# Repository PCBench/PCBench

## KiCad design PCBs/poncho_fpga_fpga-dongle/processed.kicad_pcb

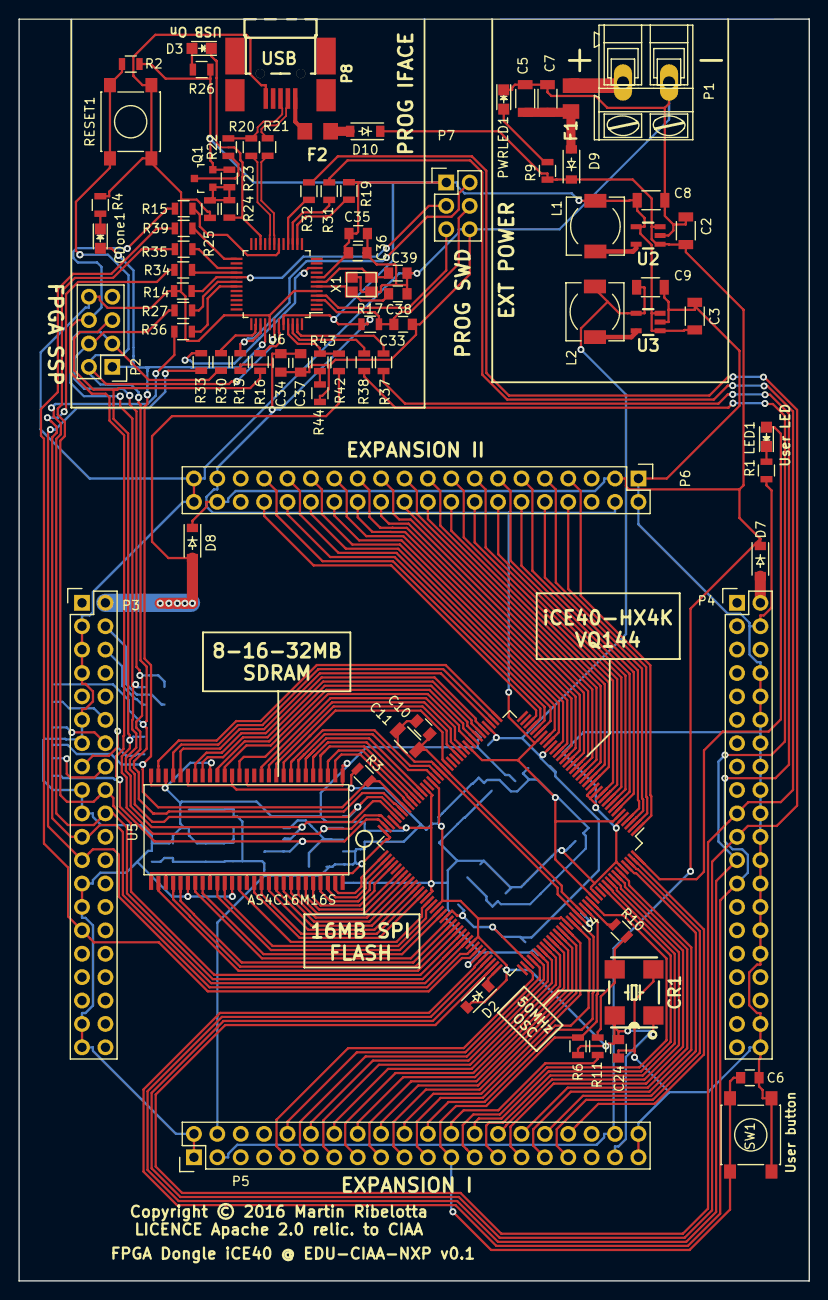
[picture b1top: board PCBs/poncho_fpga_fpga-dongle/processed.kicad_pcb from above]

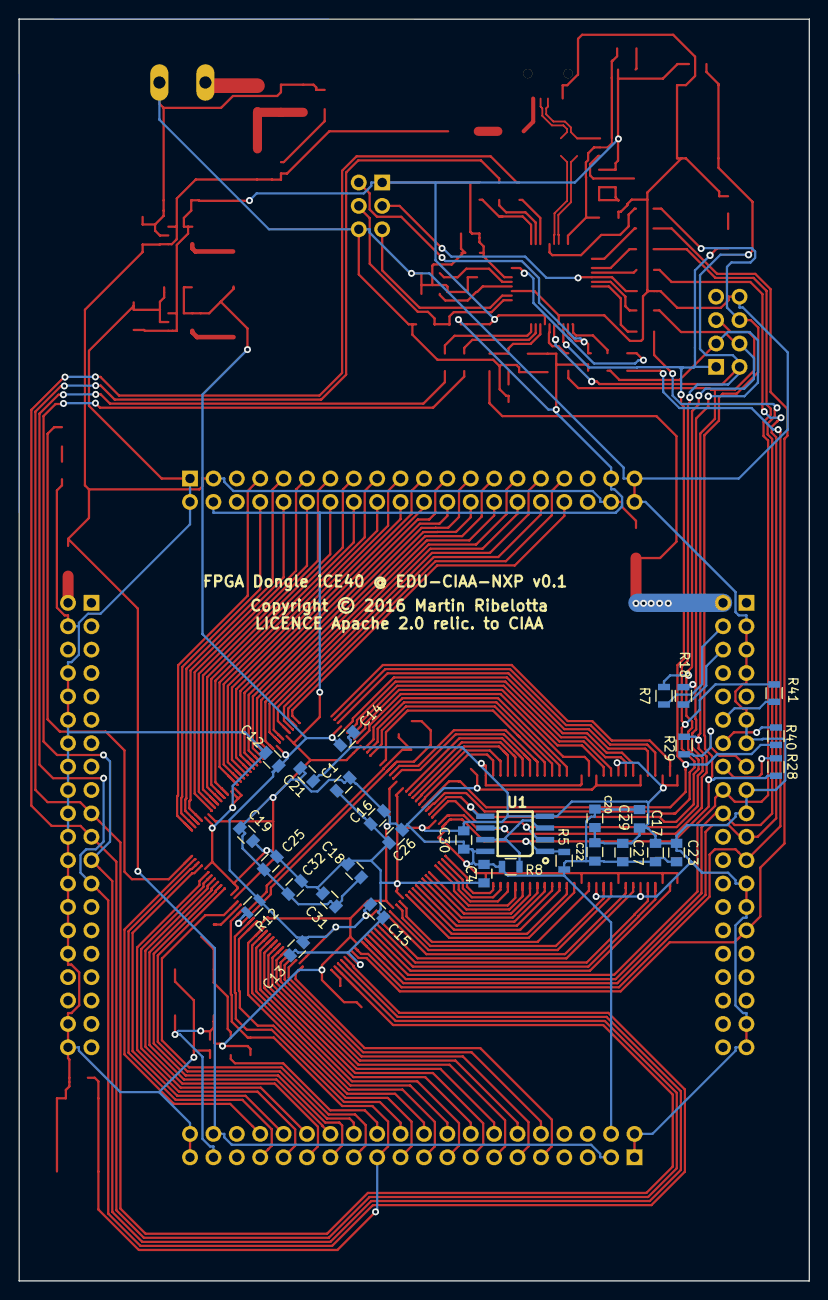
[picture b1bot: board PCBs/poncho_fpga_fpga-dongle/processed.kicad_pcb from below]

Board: 2 copper layers, 85.8 x 137.0 mm, 114 parts (31 on the bottom side), 166 nets.

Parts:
C1, C4, C6, C10, C12, C13, C14, C15, C16, C17, C18, C19, C20, C21, C22, C23, C24, C25, C26, C27, C29, C30, C31, C32, C33, C34, C36: 100nF; C_0805
C2, C3: 22uF; C_1206
C5, C7: 47uF; C_1206
C8, C9, C11: 10uF; C_1206
C35, C37: 10nF; C_0805
C38, C39: 18pF; C_0805
CDone1: LED/Green/0805; LED-0805
CR1: Oscillator-50MHZ_TXC-7W; Oscillator_7.0x5.0mm
D2, D7, D8, D9, D10: 1N5819(S4SOD-123); SOD-123
D3: LED/Red/0805; LED-0805
F1, F2: 1A; FUSE-1206
L1, L2: 2.2uH; Choke_SMD_6.3x6.3_H3
LED1: LED/Red/0805; LED-0805
P1: CONN_01X02; AK300-2
P2: PGM; Pin_Header_Straight_2x04
P3: right; Pin_Header_Straight_2x20
P4: left; Pin_Header_Straight_2x20
P5, P6: CONN_01X40; Pin_Header_Straight_2x20
P7: DBG_SWD; Pin_Header_Straight_2x03
P8: USB_PWR; USB_Mini-B-NOSILK
PWRLED1: LED/Red/0805; LED-0805
Q1: BC857; SOT-23
R1, R3, R9, R19, R24, R26: 2.2k; R_0805
R2, R5, R6, R8, R13, R14, R17, R23, R42, R43, R44: 10k; R_0805
R4, R10, R11, R15, R16, R27, R30: 22R; R_0805
R7, R12, R18, R28, R29, R31, R32, R33, R34, R35, R36, R37, R38, R39, R40, R41: 100R; R_0805
R20, R21: 33R; R_0805
R22: 1.5k; R_0805
R25: UL; R_0805
RESET1: T1107A(6x3,8x2,5MM); SW_SPST_PTS645
SW1: T1107A(6x3,8x2,5MM); SW_SPST_PTS645
U1: W25Q128FVSIG(SOIC-8_208mil); SOIC-8_208mil
U2: sc189(Z) 3.3v; SOT-23-5
U3: sc189(C) 1.2v; SOT-23-5
U4: iCE40-HX4K-TQ144; LQFP-144_20x20mm_Pitch0.5mm
U5: AS4C16M16S; TSOP_II_54
U6: LPC11U35FBD48; LQFP-48_7x7mm_Pitch0.5mm
X1: 12MHz; crystal_FA238-TSX3225

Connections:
+1V2: C9.2, C12.1, C13.1, C14.1, C15.1, L2.2, R12.1, U3.4, U4.27, U4.40, U4.92, U4.111
+3V3: C1.2, C3.2, C4.2, C8.2, C16.1, C17.1, C18.1, C19.1, C20.1, C21.1, C22.1, C23.1, C24.1, C25.1, C26.1, C27.1, C29.1, C30.1, C31.1, C32.1, C34.1, C35.1, C36.1, C37.1, CR1.1, CR1.4, D2.2, L1.2, P5.4, P5.37, P6.4, P6.37, P7.1, Q1.2, R2.2, R3.2, R5.2, R6.2, R8.1, R13.1, R17.1, R19.2, R23.1, R26.1, U1.8, U2.4, U3.1, U3.3, U4.6, U4.30, U4.46, U4.57, U4.72, U4.89, U4.100, U4.123, U4.131, U5.1, U5.3, U5.9, U5.14, U5.27, U5.43, U5.49, U6.8, U6.44
+5V: C2.2, D7.1, D8.1, D9.1, D10.1, P5.3, P5.38, P6.3, P6.38, R9.1, U2.1, U2.3
/AUX_CDONE: P3.14, R40.1
/AUX_CRESET: P3.12, R41.1
/AUX_SPI_MISO: P3.4, R7.1
/AUX_SPI_MOSI: P3.6, R18.1
/AUX_SPI_SCK: P3.15, R29.1
/AUX_SPI_SSEL: P3.16, R28.1
/BUT1: C6.2, P5.23, R6.1, SW1.2, U4.128
/CIAA_5V1: D7.2, P4.2
/CIAA_5V2: D8.2, P3.2, R42.2
/DBG_SWCLK: P7.3, R14.1, U6.29
/DBG_SWDIO: P7.2, R13.2, U6.39
/DBG_~ISP~: P7.5, U6.4
/DBG_~RST~: C33.1, P7.4, R17.2, U6.3
/D_USB_N: R21.2, U6.19
/D_USB_P: R20.2, U6.20
/EXTCLK: P5.24, R11.1
/FPGA_IO_BANK1_0: P5.9, U4.110
/FPGA_IO_BANK1_1: P5.10, U4.112
/FPGA_IO_BANK1_2: P5.11, U4.113
/FPGA_IO_BANK1_3: P5.12, U4.114
/FPGA_IO_BANK1_4: P5.13, U4.115
/FPGA_IO_BANK1_5: P5.14, U4.116
/FPGA_IO_BANK1_6: P5.15, U4.117
/FPGA_IO_BANK1_7: P5.16, U4.118
/FPGA_IO_BANK1_8: P5.17, U4.119
/FPGA_IO_BANK1_9: P5.18, U4.120
/FPGA_IO_BANK1_10: P5.19, U4.121
/FPGA_IO_BANK1_11: P5.20, U4.122
/FPGA_IO_BANK1_12: P5.21, U4.124
/FPGA_IO_BANK1_13: P5.22, U4.125
/FPGA_IO_BANK1_14: P5.25, U4.130
/FPGA_IO_BANK1_15: P5.26, U4.134
/FPGA_IO_BANK1_16: P5.27, U4.135
/FPGA_IO_BANK1_17: P5.28, U4.136
/FPGA_IO_BANK1_18: P5.29, U4.137
/FPGA_IO_BANK1_19: P5.30, U4.138
/FPGA_IO_BANK1_20: P5.31, U4.139
/FPGA_IO_BANK1_21: P5.32, U4.141
/FPGA_IO_BANK1_22: P5.33, U4.142
/FPGA_IO_BANK1_23: P5.34, U4.143
/FPGA_IO_BANK2_0: P6.7, U4.1
/FPGA_IO_BANK2_1: P6.8, U4.2
/FPGA_IO_BANK2_2: P6.9, U4.3
/FPGA_IO_BANK2_3: P6.10, U4.4
/FPGA_IO_BANK2_4: P6.11, U4.7
/FPGA_IO_BANK2_5: P6.12, U4.8
/FPGA_IO_BANK2_6: P6.13, U4.9
/FPGA_IO_BANK2_7: P6.14, U4.10
/FPGA_IO_BANK2_8: P6.15, U4.11
/FPGA_IO_BANK2_9: P6.16, U4.12
/FPGA_IO_BANK2_10: P6.17, U4.15
/FPGA_IO_BANK2_11: P6.18, U4.16
/FPGA_IO_BANK2_12: P6.19, U4.17
/FPGA_IO_BANK2_13: P6.20, U4.18
/FPGA_IO_BANK2_14: P6.21, U4.19
/FPGA_IO_BANK2_15: P6.22, U4.20
/FPGA_IO_BANK2_16: P6.23, U4.21
/FPGA_IO_BANK2_17: P6.24, U4.22
/FPGA_IO_BANK2_18: P6.25, U4.23
/FPGA_IO_BANK2_19: P6.26, U4.24
/FPGA_IO_BANK2_20: P6.27, U4.25
/FPGA_IO_BANK2_21: P6.28, U4.26
/FPGA_IO_BANK2_22: P6.29, U4.28
/FPGA_IO_BANK2_23: P6.30, U4.29
/FPGA_IO_BANK2_24: P6.31, U4.31
/FPGA_IO_BANK2_25: P6.32, U4.32
/FPGA_IO_BANK2_26: P6.33, U4.33
/FPGA_IO_BANK2_27: P6.34, U4.34
/FPGM_MISO: R27.1, U6.30
/FPGM_MOSI: R30.1, U6.38
/FPGM_SCK: R16.1, U6.43
/FPGM_SS: R15.1, U6.18
/GNDPLL: C10.1, C11.1, U4.53, U4.127
/GPIO0: P3.29, R39.2, U4.102
/I2C_SCL: P4.21, R32.2, U4.106
/I2C_SDA: P4.19, R31.2, U4.107
/LED1: LED1.2, U4.144
/P_GPIO: R39.1, U6.25
/P_RxD: R38.1, U6.46
/P_SCL: R32.1, U6.16
/P_SDA: R31.1, U6.15
/P_SPI_CLK: R36.1, U6.31
/P_SPI_MISO: R35.1, U6.27
/P_SPI_MOSI: R34.1, U6.28
/P_SPI_SS: R33.1, U6.10
/P_TxD: R37.1, U6.47
/RAM_A1: U4.76, U5.23
/RAM_A2: U4.75, U5.24
/RAM_A3: U4.74, U5.25
/RAM_A4: U4.73, U5.26
/RAM_A5: U4.64, U5.29
/RAM_A6: U4.63, U5.30
/RAM_A7: U4.62, U5.31
/RAM_A8: U4.61, U5.32
/RAM_A9: U4.60, U5.33
/RAM_A10: U4.56, U5.34
/RAM_A11: U4.78, U5.22
/RAM_A12: U4.55, U5.35
/RAM_A13: U4.52, U5.36
/RAM_A14: U4.80, U5.20
/RAM_A15: U4.79, U5.21
/RAM_CAS: U4.83, U5.17
/RAM_CKE: U4.49, U5.37
/RAM_CLK: U4.48, U5.38
/RAM_CS: U4.81, U5.19
/RAM_D0: U4.96, U5.2
/RAM_D1: U4.95, U5.4
/RAM_D2: U4.94, U5.5
/RAM_D3: U4.93, U5.7
/RAM_D4: U4.91, U5.8
/RAM_D5: U4.90, U5.10
/RAM_D6: U4.88, U5.11
/RAM_D7: U4.87, U5.13
/RAM_D8: U4.45, U5.42
/RAM_D9: U4.44, U5.44
/RAM_D10: U4.43, U5.45
/RAM_D11: U4.42, U5.47
/RAM_D12: U4.41, U5.48
/RAM_D13: U4.39, U5.50
/RAM_D14: U4.38, U5.51
/RAM_D15: U4.37, U5.53
/RAM_DQMH: U4.47, U5.39
/RAM_DQML: U4.85, U5.15
/RAM_RAS: U4.82, U5.18
/RAM_RDnWR: U4.84, U5.16
/RxD: P4.23, R38.2, U4.105
/SPI_CLK: P3.20, R36.2, U4.98
/SPI_CS: P3.23, R33.2, U4.101
/SPI_MISO: P3.18, R35.2, U4.97
/SPI_MOSI: P3.21, R34.2, U4.99
/SYSCLK: R10.1, U4.129
/TxD: P4.25, R37.2, U4.104
/USB_N: P8.2, R21.1
/USB_P: P8.3, R20.1, R22.1
/VCCPLL: C10.2, C11.2, R12.2, U4.54, U4.126
/iCE40-CDONE: CDone1.2, P2.1, R3.1, R40.2, U4.65, U6.40
/iCE40-CRESET: P2.2, R2.1, R41.2, RESET1.2, U4.66, U6.42
/iCE40-SCK: P2.5, R16.2, R29.2, U1.6, U4.70
/iCE40-SDI: P2.3, R18.2, R30.2, U1.2, U4.68
/iCE40-SDO: P2.4, R7.2, R27.2, U1.5, U4.67
/iCE40-SS_B: P2.6, R5.1, R15.2, R28.2, U1.1, U4.71
/~USB_CONNECT~: D3.1, R24.2, U6.22
GND: C1.1, C2.1, C3.1, C4.1, C5.1, C6.1, C7.1, C8.1, C9.1, C12.2, C13.2, C14.2, C15.2, C16.2, C17.2, C18.2, C19.2, C20.2, C21.2, C22.2, C23.2, C24.2, C25.2, C26.2, C27.2, C29.2, C30.2, C31.2, C32.2, C33.2, C34.2, C35.2, C36.2, C37.2, C38.2, C39.2, CR1.2, P1.1, P2.8, P3.3, P3.5, P3.7, P3.11, P3.13, P3.17, P3.19, P3.25, P3.27, P3.37, P3.39, P4.4, P4.8, P4.10, P4.12, P4.14, P4.16, P4.18, P4.20, P4.22, P4.24, P4.26, P4.28, P4.30, P4.32, P4.38, P4.40, P5.1, P5.2, P5.39, P5.40, P6.1, P6.2, P6.39, P6.40, P7.6, P8.5, PWRLED1.1, R1.2, R4.2, R14.2, R25.2, R44.1, RESET1.1, SW1.1, U1.4, U2.2, U3.2, U4.5, U4.13, U4.14, U4.59, U4.69, U4.86, U4.103, U4.132, U4.140, U5.6, U5.12, U5.28, U5.41, U5.46, U5.52, U5.54, U6.5, U6.41, X1.3
unnamed: C5.2, C7.2, D9.2, F1.2
unnamed: C38.1, U6.6, X1.2
unnamed: C39.1, U6.7, X1.1
unnamed: CDone1.1, R4.1
unnamed: CR1.3, R10.2, R11.2
unnamed: D2.1, U4.108
unnamed: D3.2, R26.2
unnamed: D10.2, F2.2
unnamed: F1.1, P1.2
unnamed: F2.1, P8.1
unnamed: L1.1, U2.5
unnamed: L2.1, U3.5
unnamed: LED1.1, R1.1
unnamed: PWRLED1.2, R9.2
unnamed: Q1.1, R23.2, R24.1, R25.1
unnamed: Q1.3, R22.2
unnamed: R8.2, U1.3, U1.7
unnamed: R19.1, U6.14
unnamed: R42.1, R43.1, U6.45
unnamed: R43.2, R44.2

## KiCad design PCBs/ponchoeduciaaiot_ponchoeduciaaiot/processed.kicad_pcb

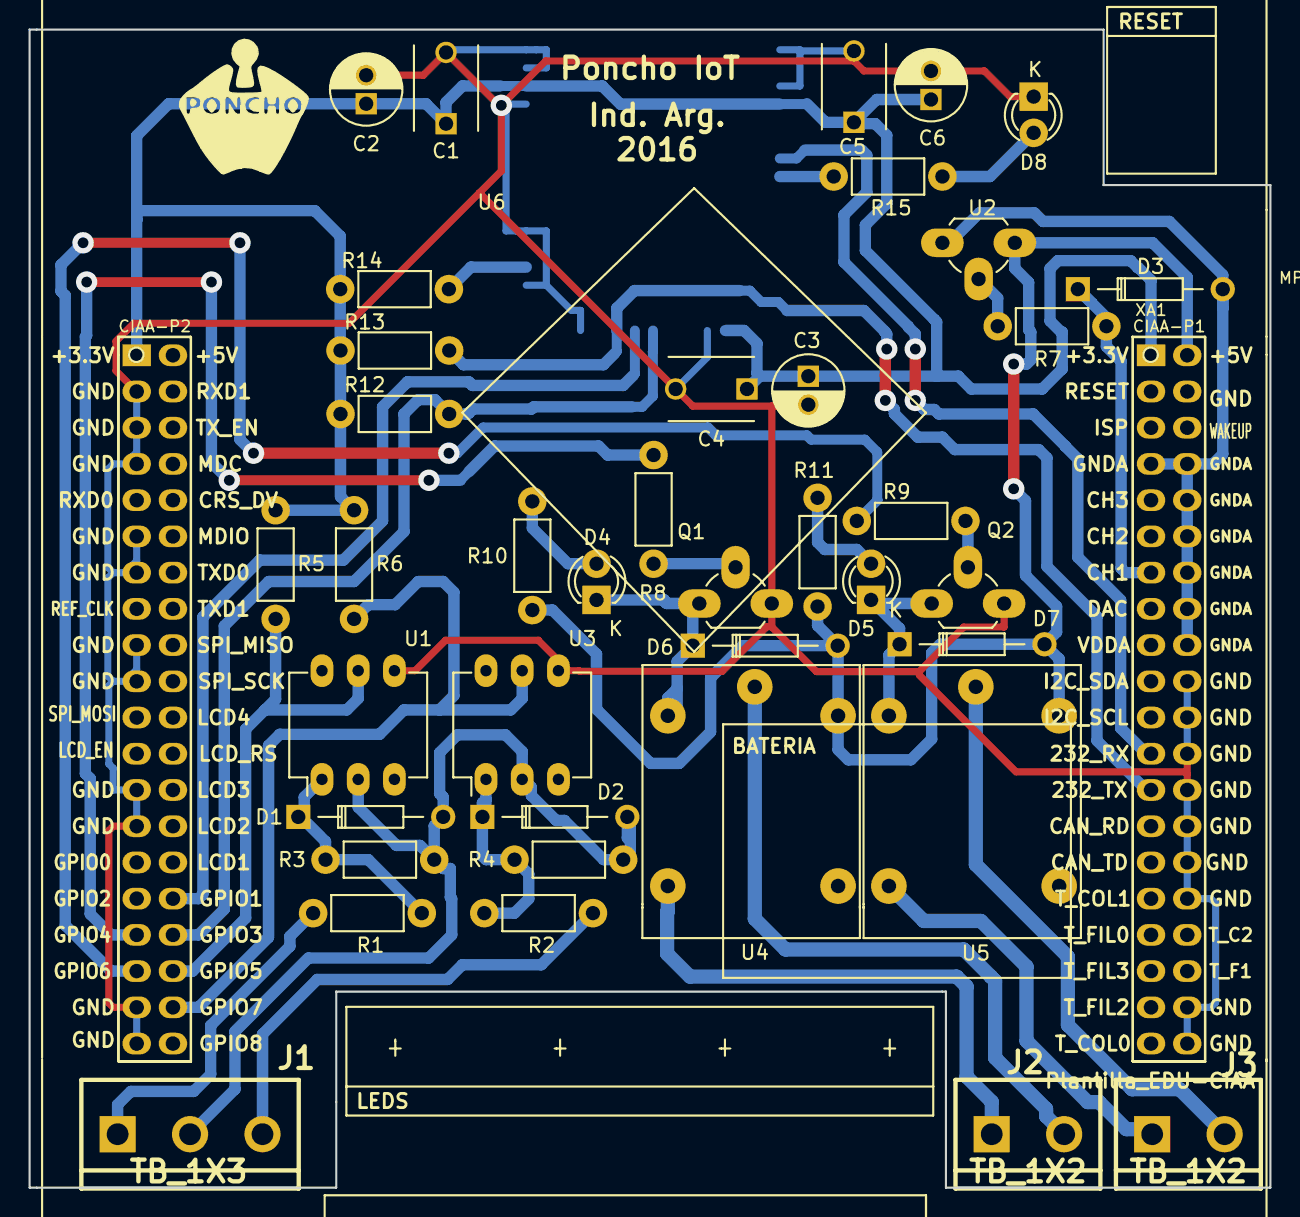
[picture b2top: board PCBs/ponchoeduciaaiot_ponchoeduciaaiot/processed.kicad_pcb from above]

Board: 2 copper layers, 87.0 x 81.2 mm, 42 parts (0 on the bottom side), 32 nets.

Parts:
C1, C4, C5: 100nF; C_Disc_D6_P5
C2, C3, C6: 2.2uF; C_Radial_D5_L11_P2
D1, D2, D6, D7: 1N4007; Diode_DO-35_SOD27_Horizontal_RM10
D3: 1N4728A; Diode_DO-35_SOD27_Horizontal_RM10
D4, D5, D8: LED; LED-3MM
J1: TB_1X3; bornier3
J2, J3: TB_1X2; bornier2
MP?: Plantilla_EDU-CIAA
Q1, Q2: BC548; TO-92_Rugged
R1, R2: 3.3k; Resistor_Horizontal_RM7mm
R3, R4: 4.7k; Resistor_Horizontal_RM7mm
R5, R6, R8, R9, R12, R14: 10k; Resistor_Horizontal_RM7mm
R7, R15: 150; Resistor_Horizontal_RM7mm
R10, R11: 330; Resistor_Horizontal_RM7mm
R13: 100k; Resistor_Horizontal_RM7mm
U1, U3: 4N25; DIP-6_W7.62mm_LongPads
U2: LM35; TO-92_Rugged
U4, U5: RELAY; Relay5vSI
U6: RN1810E; RN1810
XA1: Conn_Poncho2P_2x_20x2; Conn_Poncho_Mediano

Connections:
+3V3: C1.1, C2.1, C3.1, C4.1, C5.1, C6.1, R5.1, R6.1, R12.1, R13.1, R14.1, U6.4, U6.15, U6.35, XA1.1, XA1.41
+5V: D6.2, D7.2, R10.1, R11.1, U2.1, U4.2, U5.2, XA1.2
/ConectoresPoncho/ANALOG_IN: D3.1, R7.1, XA1.13
/ConectoresPoncho/MODULE_RESET: R12.2, U6.19, XA1.74
/ConectoresPoncho/RXD_EDUCIAA: U6.7, XA1.23
/ConectoresPoncho/TXD_EDUCIAA: R13.2, U6.21, XA1.25
/comm/CMD_CTRL: U6.20, XA1.72
/gpios/IN0: R5.2, U1.5, XA1.76
/gpios/IN1: R6.2, U3.5, XA1.78
/gpios/OUT0: R8.2, XA1.73
/gpios/OUT1: R9.2, XA1.75
GND: C1.2, C2.2, C3.2, C4.2, C5.2, C6.2, D8.1, Q1.3, Q2.3, U1.4, U3.4, U6.1, U6.3, U6.16, U6.23, U6.24, U6.27, U6.34, U6.36, U6.37, XA1.20, XA1.22, XA1.24, XA1.26, XA1.28, XA1.30, XA1.32, XA1.38, XA1.40, XA1.43, XA1.45, XA1.47, XA1.51, XA1.53, XA1.57, XA1.59, XA1.65, XA1.67, XA1.77, XA1.79
GNDA: D3.2, U2.3, XA1.7, XA1.8, XA1.10, XA1.12, XA1.14, XA1.16, XA1.18
unnamed: D1.1, R1.1, R3.1, U1.1
unnamed: D1.2, D2.2, J1.2, R3.2, R4.2, U1.2, U3.2
unnamed: D2.1, R2.1, R4.1, U3.1
unnamed: D4.1, D6.1, Q1.1, U4.1
unnamed: D4.2, R10.2
unnamed: D5.1, D7.1, Q2.1, U5.1
unnamed: D5.2, R11.2
unnamed: D8.2, R15.1
unnamed: J1.1, R1.2
unnamed: J1.3, R2.2
unnamed: J2.1, U4.4
unnamed: J2.2, U4.3
unnamed: J3.1, U5.4
unnamed: J3.2, U5.3
unnamed: Q1.2, R8.1
unnamed: Q2.2, R9.1
unnamed: R7.2, U2.2
unnamed: R14.2, U6.25
unnamed: R15.2, U6.8

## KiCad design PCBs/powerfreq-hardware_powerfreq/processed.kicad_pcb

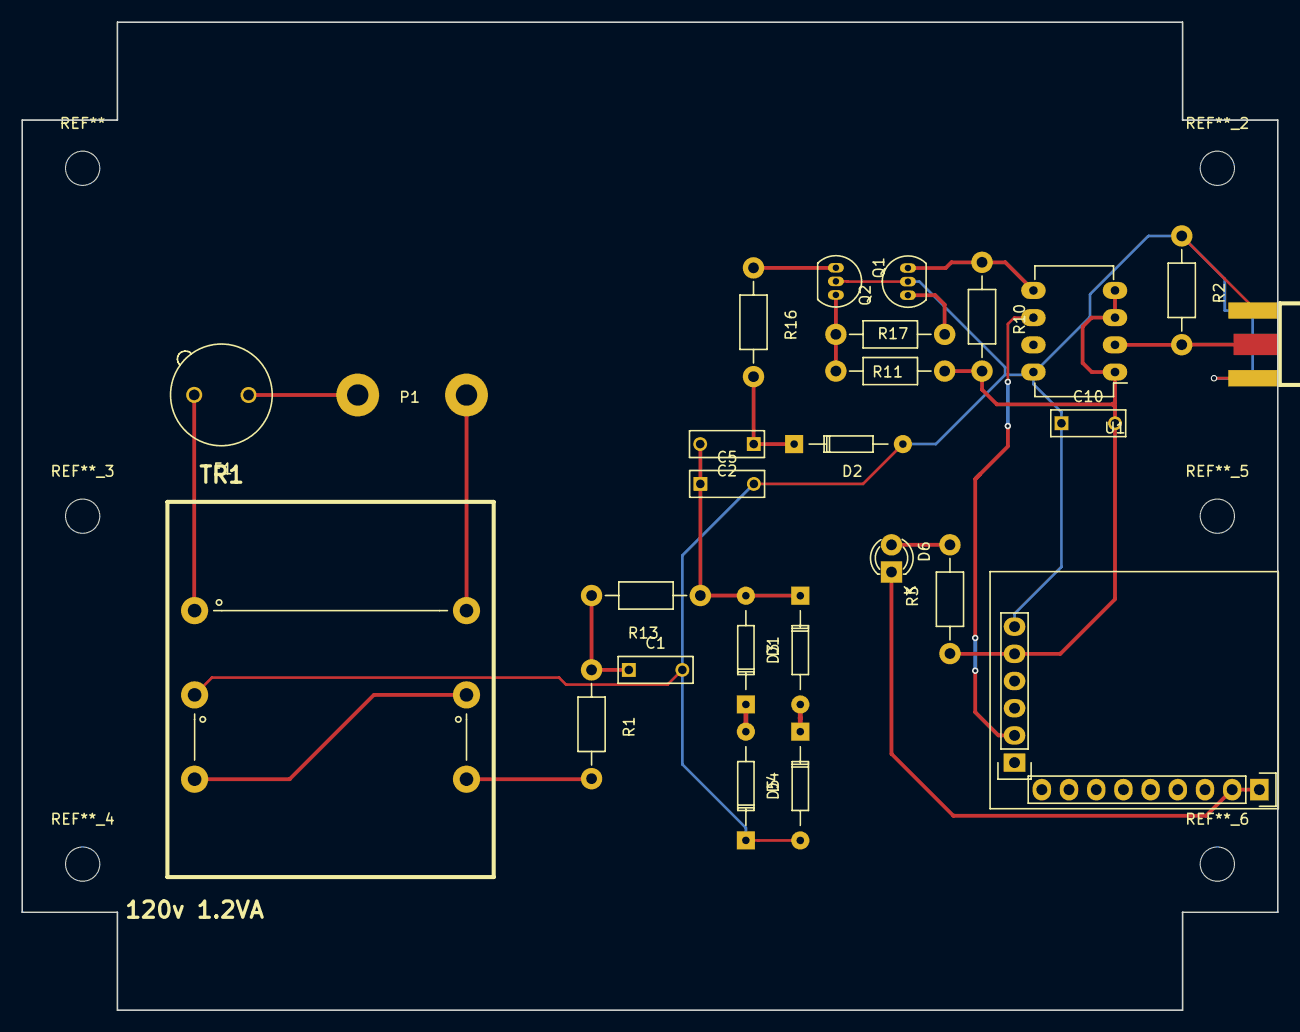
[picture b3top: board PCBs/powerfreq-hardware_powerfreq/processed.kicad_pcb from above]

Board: 2 copper layers, 117.3 x 92.3 mm, 26 parts (0 on the bottom side), 20 nets.

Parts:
C1, C10: 100nF; C_Rect_L7_W2.5_P5
C2, C5: 10nF; C_Rect_L7_W2.5_P5
D1, D2, D3, D4, D5: 1N4148; Diode_DO-35_SOD27_Horizontal_RM10
D6: LED; LED-3MM
F1: 50mA; Fuseholder_Fuse_TR5_Littlefuse-No560_No460
J1: SMA; SMA_EDGE
P1: CONN_01X03; WireConnection_2.00mmDrill
Q1, Q2: 2N3904; TO-92_Inline_Narrow_Oval
R1: 2k 1W; Resistor_Horizontal_RM10mm
R2: 51; Resistor_Horizontal_RM10mm
R3, R10, R16: 1k; Resistor_Horizontal_RM10mm
R11: 2.2k; Resistor_Horizontal_RM10mm
R13: 20k 2W; Resistor_Horizontal_RM10mm
R17: 250; Resistor_Horizontal_RM10mm
TR1: 120v 1.2VA; 161E120
U1: picPET-03; DIP-8_W7.62mm_LongPads
U2: MIKROE-483; mikroe-483

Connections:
10MHz: J1.1, R2.2, U1.2
60PPS: Q2.3, R10.1, U1.5
+3V3: C10.2, R3.1, R10.2, R17.2, U1.1, U1.3, U1.4, U2.2-5
CLAMP: C2.2, C5.1, D1.2, D3.1, R13.1
GND: C1.2, C5.2, C10.1, D2.2, D4.1, D5.2, J1.0, J1.2, Q1.2, Q2.2, R2.1, TR1.3, U1.8, U2.2-6
unnamed: C1.1, R1.1, R13.2
unnamed: C2.1, D2.1, R16.2
unnamed: D1.1, D4.2
unnamed: D3.2, D5.1
unnamed: D6.1, U2.3-1, U2.3-2
unnamed: D6.2, R3.2
unnamed: F1.1, P1.1
unnamed: F1.2, TR1.1
unnamed: P1.2, TR1.2
unnamed: Q1.1, R16.1
unnamed: Q2.1, R11.1
unnamed: R1.2, TR1.6
unnamed: TR1.4, TR1.5
SERIAL_RX: U1.6, U2.2-2
TRIG: Q1.3, R11.2, R17.1

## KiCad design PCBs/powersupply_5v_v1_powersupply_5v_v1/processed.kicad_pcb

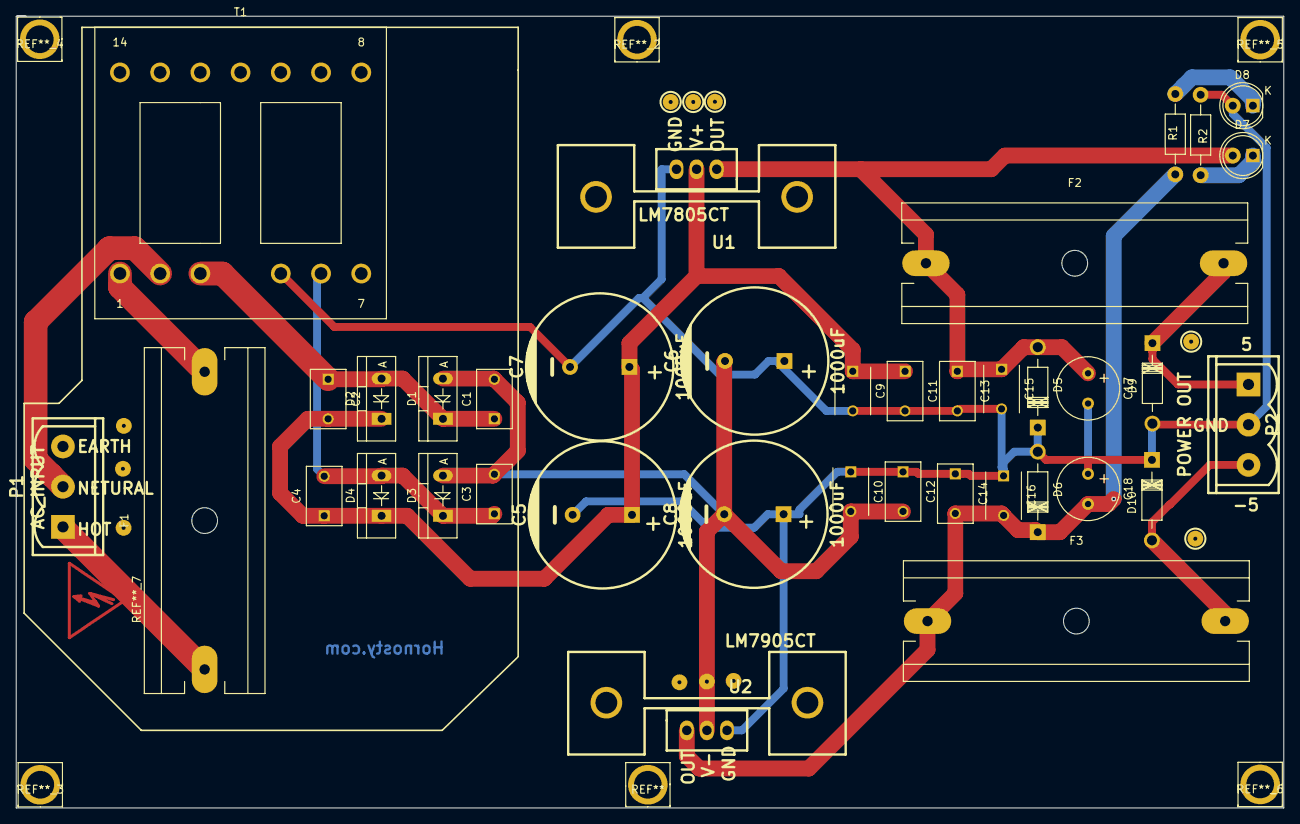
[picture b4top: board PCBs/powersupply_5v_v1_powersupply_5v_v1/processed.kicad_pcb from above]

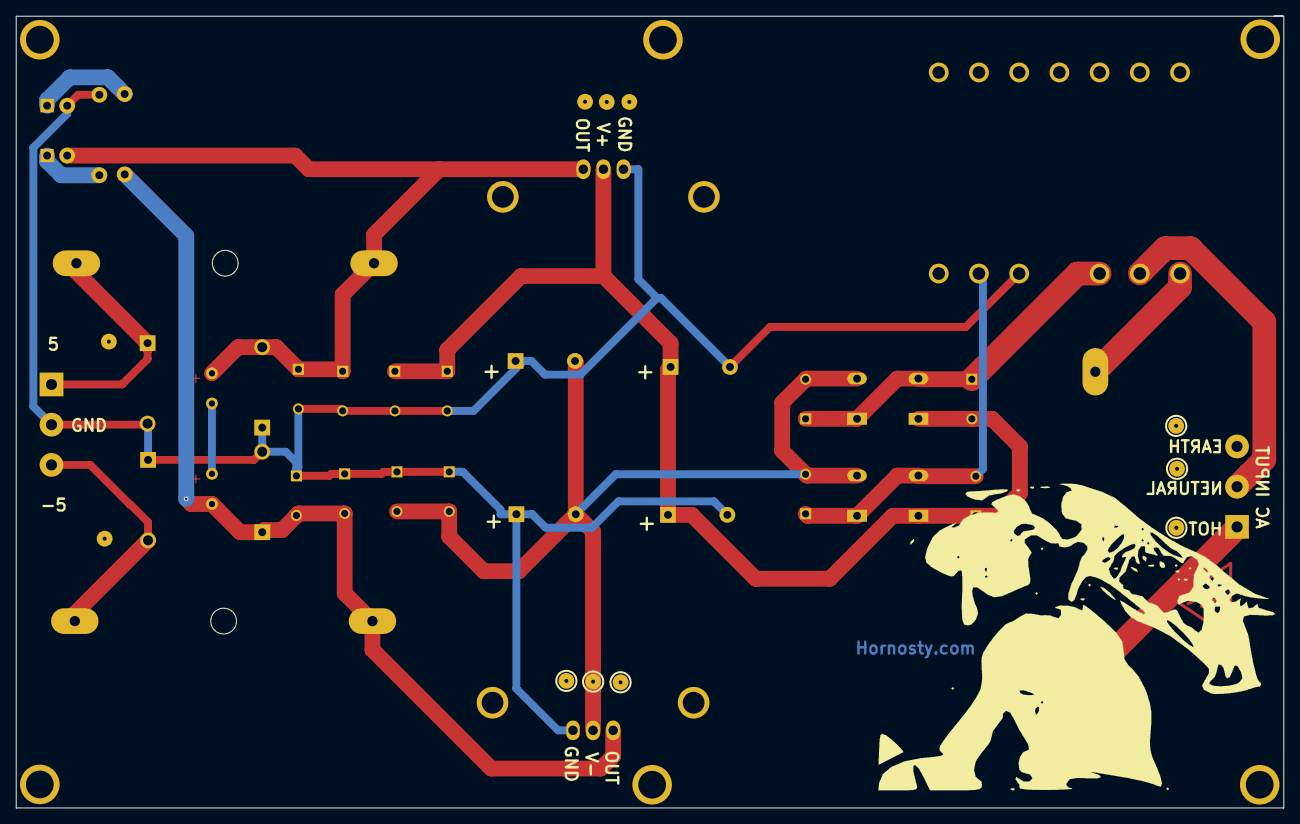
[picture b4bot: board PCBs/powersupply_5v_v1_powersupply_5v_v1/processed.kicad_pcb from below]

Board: 2 copper layers, 160.1 x 100.0 mm, 49 parts (6 on the bottom side), 14 nets.

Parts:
C1, C2, C3, C4: C_Small; C_Disc_D7.5_P5
C5, C6, C7, C8: 1000uF; CP_18x16mm
C9, C10, C15, C16: 10nF; C_Disc_D6_P5
C11, C12, C13, C14: 100nF; C_Disc_D7.5_P5
C17, C18: 470uF; Elko_vert_11.5x8mm_RM3.5
D1, D2, D3, D4: MUR860G; Diode_TO-220_Vertical
D5, D6: TVS; Diode_DO-41_SOD81_Horizontal_RM10
D7, D8: LED; LED-5MM
D9, D10: 1N4008; Diode_DO-41_SOD81_Horizontal_RM10
F1, F2, F3: FUSE; Fuseholder6x32_Horiz_Open_Schurter0031-8002
P1: AC_INPUT; mstbva_2,5%2f3-g-5,08
P2: POWER OUT; mstbva_2,5%2f3-g-5,08
R1: R; Resistor_Horizontal_RM10mm
R2: R_Small; Resistor_Horizontal_RM10mm
T1: TRANSFO2; ETD29_13Pin_Horizontal_EPCOS-B66359A1013T
U1: LM7805CT; to220_std_14cw
U2: LM7905CT; to220_std_14cw
pad_2mm, pad_2mm_2, pad_2mm_3, pad_2mm_4, pad_2mm_5, pad_2mm_6, pad_2mm_7, pad_2mm_8, pad_2mm_9, pad_2mm_10, pad_2mm_11: VAL**; pad_2mm

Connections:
/HOT: F1.1, P1.1
/NETURAL: P1.2, T1.2
/REG_+5V: D9.1, F2.2, P2.1
/REG_-5V: D10.2, F3.2, P2.3
/V+: C2.2, C4.1, C5.1, C7.1, C9.1, C11.1, D2.1, D4.1, U1.2
/V-: C1.2, C3.2, C6.2, C8.2, C10.2, C12.2, D1.2, D3.2, U2.2
GNDPWR: C5.2, C6.1, C7.2, C8.1, C9.2, C10.1, C11.2, C12.1, C13.2, C14.1, C15.2, C16.1, C17.2, C18.1, D5.1, D6.2, D8.2, D9.2, D10.1, P2.2, R1.2, T1.5, U1.1, U2.1
unnamed: C1.1, C2.1, D1.1, D2.2, T1.3
unnamed: C3.1, C4.2, D3.1, D4.2, T1.6
unnamed: C13.1, C15.1, C17.1, D5.2, D7.2, F2.1, U1.3
unnamed: C14.2, C16.2, C18.2, D6.1, F3.1, R2.2, U2.3
unnamed: D7.1, R1.1
unnamed: D8.1, R2.1
unnamed: F1.2, T1.1

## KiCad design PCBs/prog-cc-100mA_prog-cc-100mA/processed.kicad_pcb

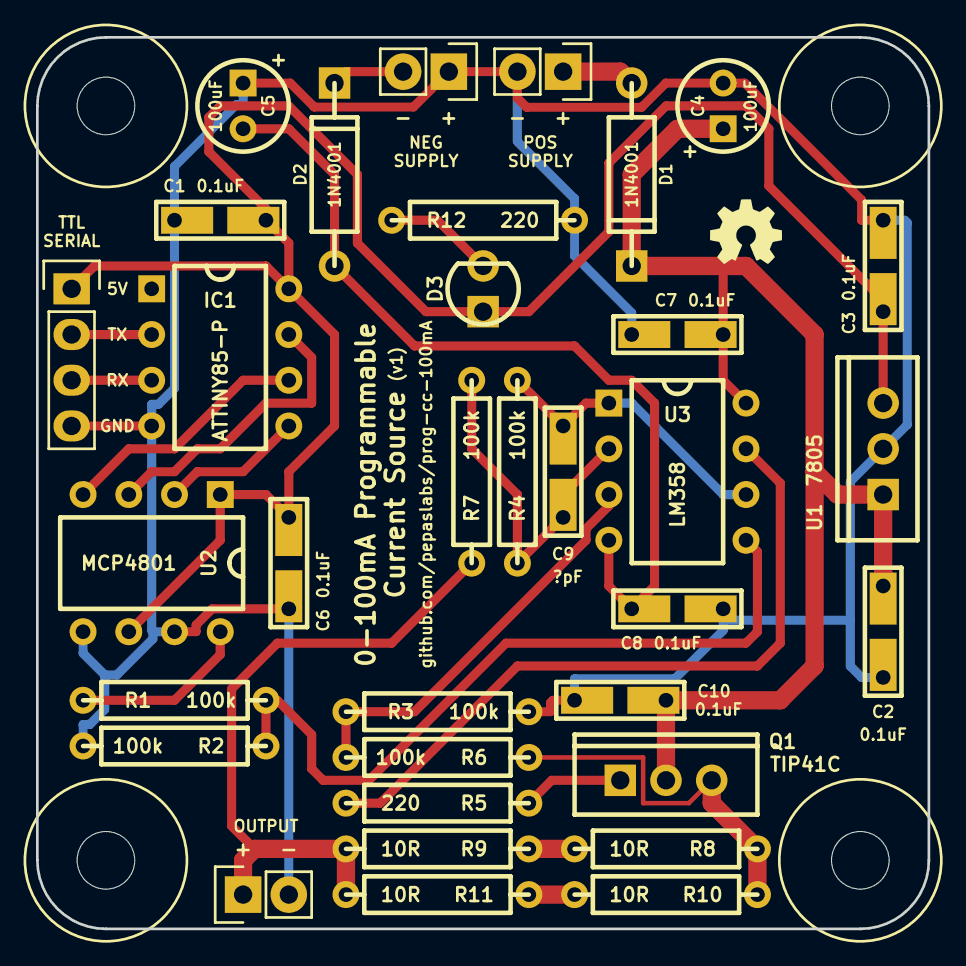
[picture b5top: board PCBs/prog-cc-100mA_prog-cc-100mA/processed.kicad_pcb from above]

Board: 2 copper layers, 49.5 x 49.5 mm, 38 parts (0 on the bottom side), 23 nets.

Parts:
C1, C2, C3, C6, C7, C8, C10: 0.1uF; CERCAP_2_059B_0805
C4, C5: 100uF; ELCAP_10_20_V_059A
C9: ?pF; CERCAP_2_059B_0805
D1, D2: 1N4001; DIODE_1A_069A_PL
D3: LED; LED_3MM_069A
H***: Val**; hole_M3_NPTH
H***_2, H***_3, H***_4: Val**; hole_M3_NPTH
IC1: ATTINY85-P; DIP8_059A_PL
P1, P2, P3: CONN_01X02; Pin_Header_Straight_1x02
P4: CONN_01X04; Pin_Header_Straight_1x04
Q1: TIP41C; TO-220_V_069A
R1, R2, R3, R4, R6, R7: 100k; R_AXIAL_0W25_059A_PL
R5, R12: 220; R_AXIAL_0W25_059A_PL
R8, R9, R10, R11: 10R; R_AXIAL_0W25_059A_PL
U1: 7805; TO-220_V_069A
U2: MCP4801; DIP8_059A_PL
U3: LM358; DIP8_059A_PL

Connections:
+5V: C1.1, C3.1, C6.1, D3.1, IC1.8, P4.1, U1.3, U2.1, U2.6
+V: C2.1, C4.1, C7.1, C10.1, D1.2, Q1.2, U1.1, U3.8
-V: C5.2, C8.2, D2.1, U3.4
CS: IC1.5, U2.2
GND: C1.2, C2.2, C3.2, C4.2, C5.1, C6.2, C7.2, C8.1, C10.2, IC1.4, P1.2, P2.1, P3.2, P4.4, R2.2, R3.2, R12.2, U1.2, U2.5, U2.7
unnamed: C9.1, R4.1, R7.2, U3.2
unnamed: C9.2, R4.2, U3.1, U3.6
unnamed: D1.1, P1.1
unnamed: D2.2, P2.2
unnamed: D3.2, R12.1
unnamed: Q1.1, R5.1
unnamed: Q1.3, R6.1, R8.1, R10.1
unnamed: R1.1, U2.8
unnamed: R1.2, R2.1, U3.5
unnamed: R3.1, R6.2, U3.3
unnamed: R5.2, U3.7
unnamed: R8.2, R9.1
unnamed: R10.2, R11.1
Out: P3.1, R7.1, R9.2, R11.2
RX: IC1.3, P4.3
SCK: IC1.7, U2.3
SDO: IC1.6, U2.4
TX: IC1.2, P4.2

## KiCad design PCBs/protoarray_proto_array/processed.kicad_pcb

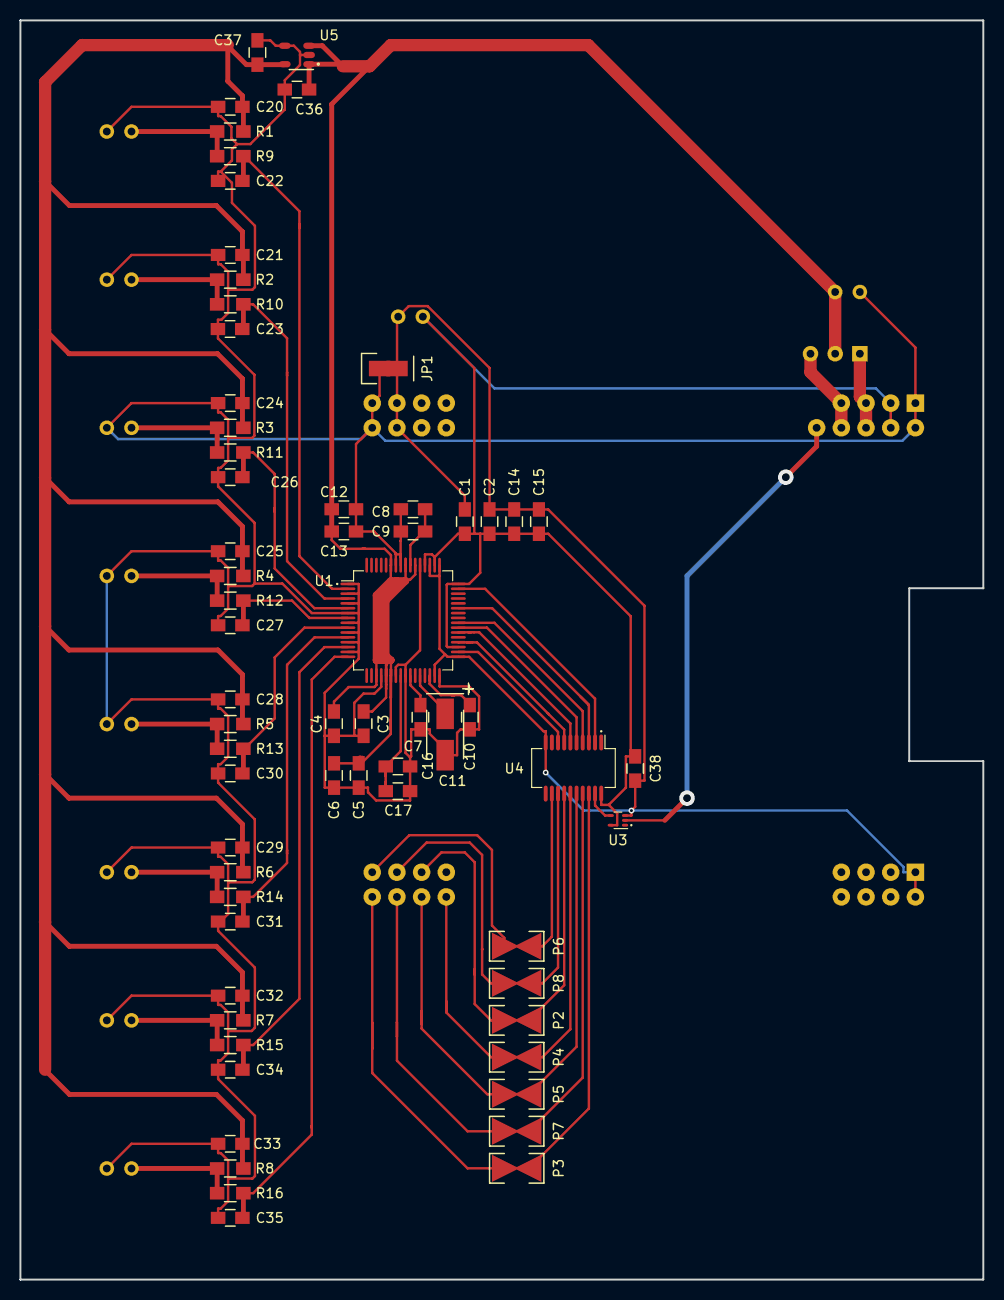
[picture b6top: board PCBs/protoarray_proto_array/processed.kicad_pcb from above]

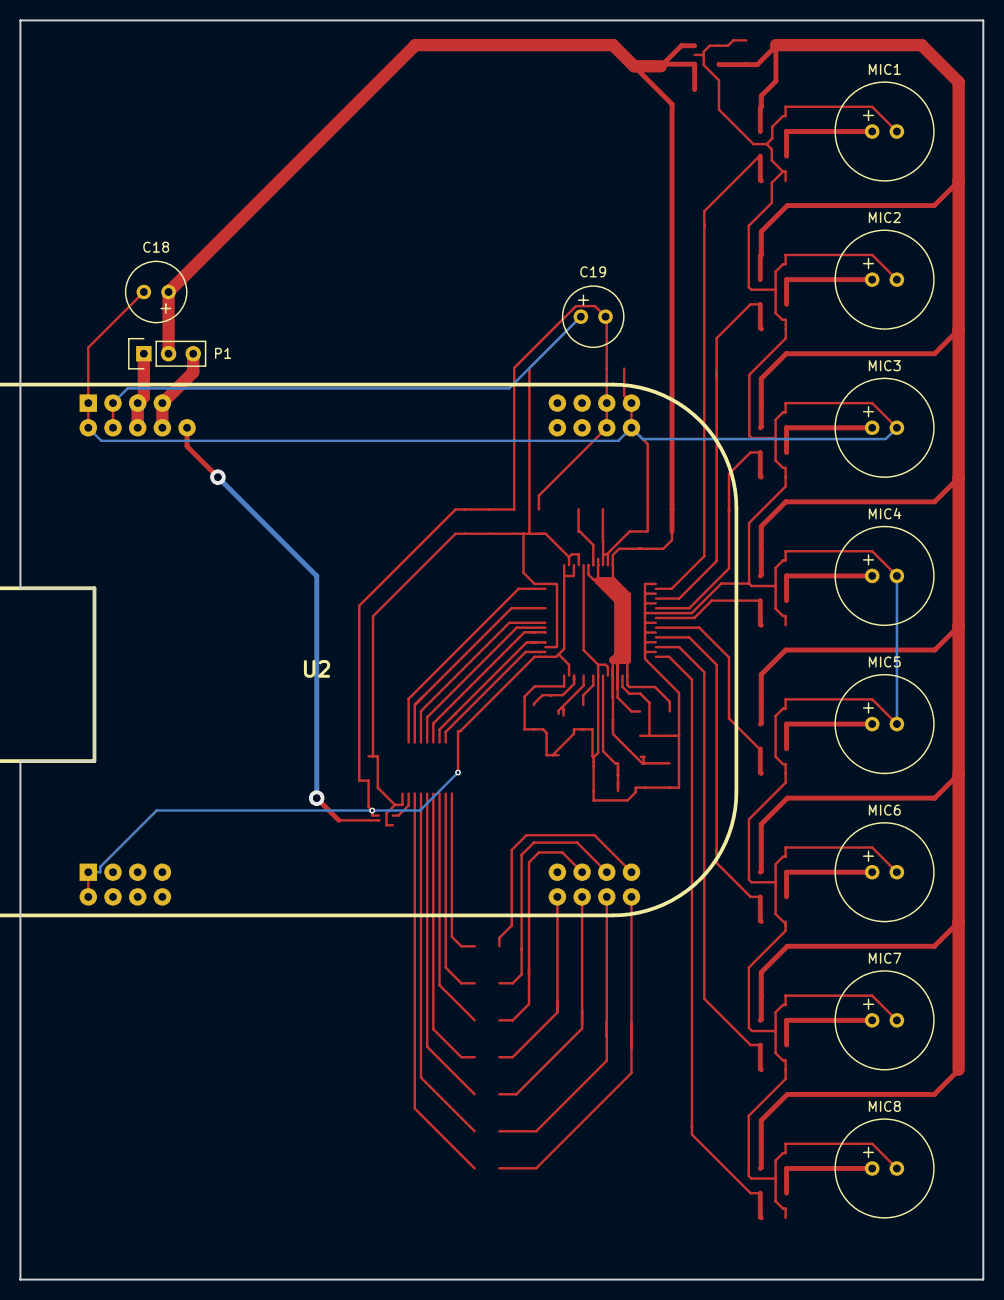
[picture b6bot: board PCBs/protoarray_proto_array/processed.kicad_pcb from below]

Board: 2 copper layers, 99.1 x 129.5 mm, 76 parts (12 on the bottom side), 51 nets.

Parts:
C1, C3, C5, C7, C8, C10, C12, C14, C16, C20, C21, C22, C23, C24, C25, C26, C27, C28, C29, C30, C31, C32, C33, C34, C35, C36, C37, C38: 1uF; C_0805_HandSoldering
C2, C4, C6, C9, C13, C15, C17: 0.1uF; C_0805_HandSoldering
C11: 22uF; TantalC_SizeB_EIA-3528_HandSoldering
C18, C19: 100uF; Elko_vert_11.2x6.3mm_RM2.5_CopperClear
JP1: JUMPER; Jumper
MIC1, MIC2, MIC3, MIC4, MIC5, MIC6, MIC7, MIC8: ELECTRET; Electret_1mm
P1: CONN_01X03; Pin_Header_01x03
P2, P3, P4, P5, P6, P7, P8: CONN_01X02; Pin_Header_NC_01x02
R1, R2, R3, R4, R5, R6, R7, R8, R9, R10, R11, R12, R13, R14, R15, R16: 10k; R_0805_HandSoldering
U1: ADS131E08; LQFP-64_12x12_Pitch0.5mm_NoFid
U2: BEAGLEBONEBLACK; beagleboneblack_custom
U3: 741G04; SOTFL-5_160x50_Pitch0.5
U4: 743245; SOP-20_600x175_Pitch0.635
U5: TLV70233DBV; SOT-23-5

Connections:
+3V3: C20.1, C21.1, C24.1, C25.1, C28.1, C29.1, C32.1, C33.1, C37.1, R1.1, R2.1, R3.1, R4.1, R5.1, R6.1, R7.1, R8.1, U5.5
/ADS_CS: U1.39, U4.5
/ADS_DIN: U1.34, U4.8
/ADS_DOUT: U1.43, U4.3
/ADS_DRDY: U1.47, U4.2
/ADS_RESET: U1.36, U4.7
/ADS_SCLK: U1.40, U4.4
/ADS_START: U1.38, U4.6
/BBB_SYS_5V: P1.3, U2.C7, U2.C8
/BBB_VDD_5V: P1.1, U2.C5, U2.C6
/MIC_1: C22.2, R9.1, U1.2
/MIC_2: C23.2, R10.1, U1.4
/MIC_3: C26.2, R11.1, U1.6
/MIC_4: C27.2, R12.1, U1.8
/MIC_5: C30.2, R13.1, U1.10
/MIC_6: C31.2, R14.1, U1.12
/MIC_7: C34.2, R15.1, U1.14
/MIC_8: C35.2, R16.1, U1.16
/PRU1_0: P6.2, U2.B45
/PRU1_1: P3.2, U2.B46
/PRU1_2: P8.2, U2.B43
/PRU1_3: P7.2, U2.B44
/PRU1_4: P2.2, U2.B41
/PRU1_5: P5.2, U2.B42
/PRU1_7: P4.2, U2.B40
/SYS_RESETn: U2.C10, U3.2
/VREFP: C16.1, C17.1, U1.24
AGND: C3.2, C4.2, C5.2, C6.2, C7.2, C8.2, C9.2, C10.2, C11.2, C12.2, C13.2, C16.2, C17.2, C18.2, C20.2, C21.2, C22.1, C23.1, C24.2, C25.2, C26.1, C27.1, C28.2, C29.2, C30.1, C31.1, C32.2, C33.2, C34.1, C35.1, C36.2, C37.2, JP1.1, MIC1.2, MIC2.2, MIC3.2, MIC4.2, MIC5.2, MIC6.2, MIC7.2, MIC8.2, U1.1, U1.3, U1.5, U1.7, U1.9, U1.11, U1.13, U1.15, U1.20, U1.23, U1.25, U1.32, U1.53, U1.57, U1.58, U2.C1, U2.C2, U2.C45, U2.C46, U5.2, U5.4
AVDD: C3.1, C4.1, C5.1, C6.1, C12.1, C13.1, C18.1, C36.1, P1.2, U1.19, U1.21, U1.22, U1.54, U1.56, U1.59, U5.1, U5.3
DGND: C1.2, C2.2, C14.2, C15.2, C19.2, C38.2, JP1.2, U1.31, U1.33, U1.49, U1.51, U2.B1, U2.B2, U2.C43, U2.C44, U3.3, U4.10
DVDD: C1.1, C2.1, C14.1, C15.1, C19.1, C38.1, U1.35, U1.48, U1.50, U1.52, U2.C3, U2.C4, U3.5, U4.20
unnamed: C7.1, U1.26
unnamed: C8.1, C9.1, U1.55
unnamed: C10.1, U1.30
unnamed: C11.1, U1.28
unnamed: MIC1.1, R1.2, R9.2
unnamed: MIC2.1, R2.2, R10.2
unnamed: MIC3.1, R3.2, R11.2
unnamed: MIC4.1, R4.2, R12.2
unnamed: MIC5.1, R5.2, R13.2
unnamed: MIC6.1, R6.2, R14.2
unnamed: MIC7.1, R7.2, R15.2
unnamed: MIC8.1, R8.2, R16.2
unnamed: P2.1, U4.14
unnamed: P3.1, U4.18
unnamed: P4.1, U4.15
unnamed: P5.1, U4.16
unnamed: P6.1, U4.12
unnamed: P7.1, U4.17
unnamed: P8.1, U4.13
unnamed: U3.4, U4.19

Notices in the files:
PCBs/poncho_fpga_fpga-dongle/processed.kicad_pcb:
Copyright © 2016 Martin Ribelotta
PCBs/ponchoeduciaaiot_ponchoeduciaaiot/processed.kicad_pcb:
License: GPL3
